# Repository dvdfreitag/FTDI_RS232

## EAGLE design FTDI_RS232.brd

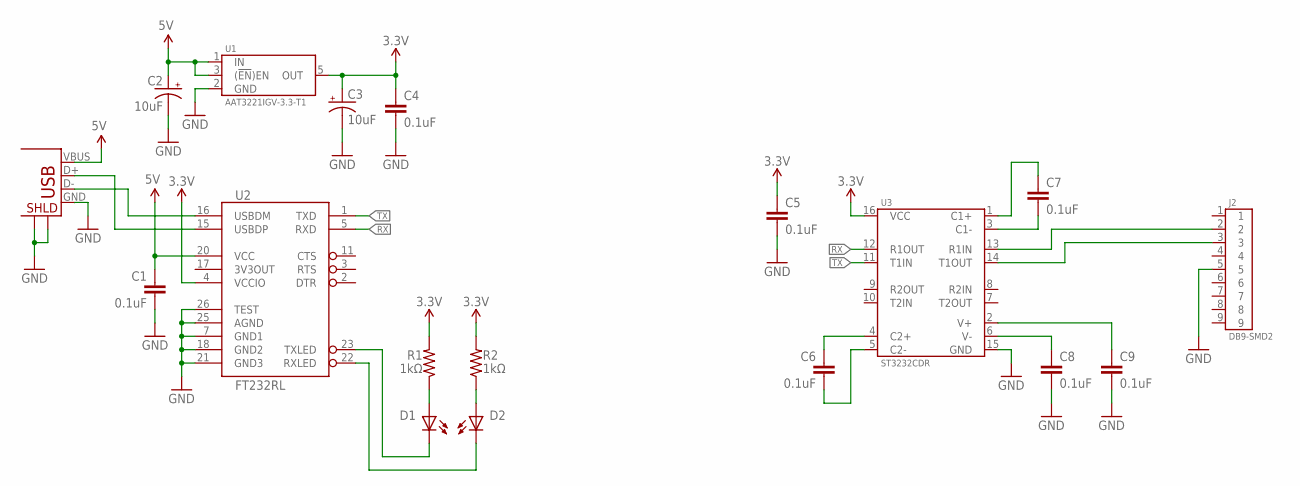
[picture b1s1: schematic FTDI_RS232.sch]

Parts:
C1, C4, C5, C6, C7, C8, C9: 0.1uF; 0805
C2, C3: 10uF; 0805-CAP_POL
D1, D2: LED-0805; 0805-LED
J1: USB+SHIELD; USB-B-PTH
J2: DB9-SMD2; DB9_SMD2
R1, R2: 1kΩ; 0805-RES
U1: AAT3221IGV-3.3-T1; SOT23-5
U2: FT232RL; SSOP28DB
U3: ST3232CDR; SOIC-16

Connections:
3.3V: C3.A (+), C4.1, C5.1, R1.2, R2.2, U1.5 (OUT), U2.4 (VCCIO), U3.16 (VCC)
5V: C1.1, C2.A (+), J1.VBUS, U1.1 (IN), U1.3 ((!EN!)EN), U2.20 (VCC)
D_N: J1.D-, U2.16 (USBDM)
D_P: J1.D+, U2.15 (USBDP)
GND: C1.2, C2.C (-), C3.C (-), C4.2, C5.2, C8.2, C9.2, J1.GND, J1.S1, J1.S2, J2.5, U1.2 (GND), U2.7 (GND1), U2.18 (GND2), U2.21 (GND3), U2.25 (AGND), U2.26 (TEST), U3.15 (GND)
unnamed: C6.1, U3.4 (C2+)
unnamed: C6.2, U3.5 (C2-)
unnamed: D2.A, R2.1
unnamed: D1.A, R1.1
unnamed: D1.C, U2.23 (TXLED)
unnamed: D2.C, U2.22 (RXLED)
unnamed: C8.1, U3.6 (V-)
unnamed: C9.1, U3.2 (V+)
unnamed: J2.2, U3.13 (R1IN)
unnamed: C7.2, U3.3 (C1-)
unnamed: C7.1, U3.1 (C1+)
unnamed: J2.3, U3.14 (T1OUT)
RX: U2.5 (RXD), U3.12 (R1OUT)
TX: U2.1 (TXD), U3.11 (T1IN)

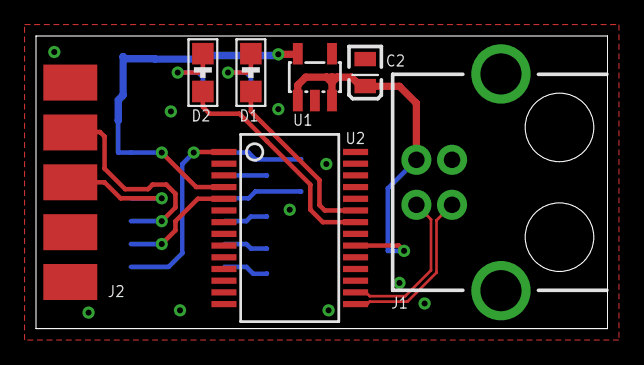
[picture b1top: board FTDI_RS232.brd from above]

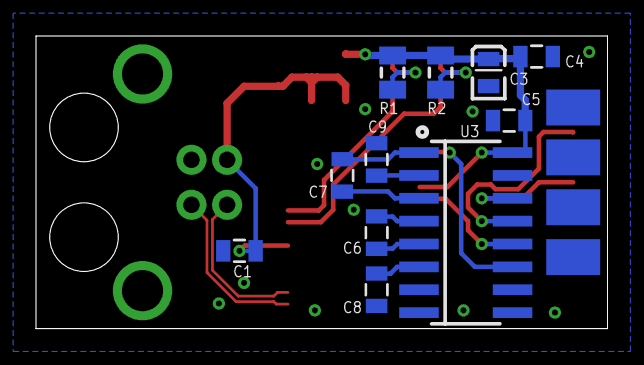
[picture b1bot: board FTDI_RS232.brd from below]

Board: 2 copper layers, 31.8 x 16.3 mm, 18 parts (11 on the bottom side), 19 nets.

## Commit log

2016-08-12 Create LICENSE
2016-08-12 Added pdf documents

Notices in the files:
parts and their libraries:
SparkFun-DigitalIC: Licensing: CC v3.0 Share-Alike You are welcome to use this library for commercial purposes.
